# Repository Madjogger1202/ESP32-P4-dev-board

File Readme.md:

# ESP32-P4-dev-board

> High-performance vision and control board based on **ESP32-P4 (32 MB internal RAM)**.  
> Designed as a modern replacement for **OpenMV-style boards** built on STM32H7,  
> with integrated USB interfaces, Wi-Fi, camera connector, and expansion ports.

---

## Overview

ESP32-P4-dev-board combines imaging, communication, and compute capabilities in a single compact platform.  
The board supports **MIPI camera modules**, **microSD storage**, **Wi-Fi via ESP-WROOM-02**, and multiple USB interfaces for flexible development and deployment.

---

## Key Features

- **Main MCU:** ESP32-P4 (dual-core, 32 MB integrated PSRAM)
- **External Flash:** GD25Q256EYIGR (32 MByte QSPI)
- **Wi-Fi module:** ESP-WROOM-02 (UART connection to P4)
- **Distance sensor:** VL53L0CXV0DH1 (time-of-flight)
- **Camera interface:** DF30FC-24DS-0.4V_81 (2-lane MIPI, Raspberry Pi-compatible)
- **microSD slot:** 4-bit SDIO
- **5× WS2812B RGB LEDs** — for illumination or status visualization
- **Three USB ports:**
  - **USB-UART** (CH343P, auto-programming transistors)
  - **USB FS** — GPIO 24 / 25
  - **USB HS** — native high-speed
- **Expansion:**
  - Unused GPIOs routed to headers
  - Dedicated UART and I²C headers for peripheral modules
- **Design:** fully compliant with **ГОСТ** electrical documentation standards

---

## MCU Comparison — ESP32-P4 vs STM32H743 (OpenMV reference)

| Feature | **ESP32-P4** | **STM32H743 (OpenMV)** |
|:--|:--|:--|
| Architecture | Dual-core Xtensa LX7 | Single-core ARM Cortex-M7 |
| Clock frequency | up to **400 MHz** | up to **480 MHz** |
| Internal RAM | **32 MB unified PSRAM** | **1 MB SRAM** |
| External memory | QSPI Flash (32 MB) | QSPI Flash (32 MB external PSRAM optional) |
| Floating-point | Yes, single precision | Yes, single/double precision |
| SIMD / Vector | Yes (DSP extensions) | Yes |
| MIPI Camera | **2-lane CSI** | Parallel DCMI only |
| USB | **Dual USB (FS + HS)** | USB FS only |
| Wi-Fi / BT | External (ESP-WROOM-02) | None |
| Power domains | Integrated PMU | External regulators |
| Peripherals | I²S, SPI, I²C, SDIO, PWM, UART | I²S, SPI, I²C, SDIO, UART |
| Typical RAM bandwidth | ~3.2 GB/s internal | ~200 MB/s SRAM |
| Cost efficiency | Higher performance per $ | Mature ecosystem |
| OpenMV compatibility | Target-compatible (similar form-factor) | Native reference platform |

> ✅ **ESP32-P4** outperforms STM32H7 in memory bandwidth and integration,  
> enabling higher-resolution image processing and neural inference directly on-board.

---

## Power & Interfaces

| Function | Interface | Notes |
|:--|:--|:--|
| Power | USB-C / USB-UART | 5 V input |
| Programming | via CH343P (auto-boot/reset) | |
| Storage | microSD (SDIO 4-bit) | High-speed mode supported |
| Wi-Fi | ESP-WROOM-02 | UART link |
| Camera | MIPI-CSI 2-lane | Supports low-cost Pi-compatible modules |
| Distance sensor | VL53L0CXV0DH1 | I²C |
| LEDs | WS2812B × 5 | GPIO-controlled |
| Expansion | UART, I²C, GPIO headers | For custom peripherals |

---

## Typical Applications

- Embedded **computer-vision** systems  
- **Robot control** and sensor fusion nodes  
- **Edge AI** and object-tracking experiments  
- Low-cost camera systems for prototyping and teaching  
- Drop-in **OpenMV replacement** with better memory and bandwidth

---

## Quick Use

1. Connect via **USB-UART** port for programming (auto-boot handled by CH343P).  
2. Flash firmware (ESP-IDF, MicroPython, or custom).  
3. Connect MIPI camera module to DF30FC-24DS connector.  
4. Optionally mount **microSD** for data logging.  
5. Power from any USB port (5 V).  
6. Use WS2812B LEDs for illumination or debug status.

---

## Notes

- Default PD profile: **5 V** (no PD negotiation required).  
- **ESP-WROOM-02** communicates only over UART (no SPI bridge).  
- **MIPI interface** is 2-lane, matching most low-cost Raspberry Pi-compatible cameras.  
- **Schematics and layout** follow ГОСТ formatting.  
- **All unconnected GPIOs** are routed to headers for expansion.

---

## Images
*(to be added)*  
- Board top view  
- Board bottom view  
- Top layer routing  

---

## ⚠️ Status

> ⚠️ This hardware is **unverified** — first prototype **not yet tested**.  
> Electrical connections and functionality may require validation and tuning.

---

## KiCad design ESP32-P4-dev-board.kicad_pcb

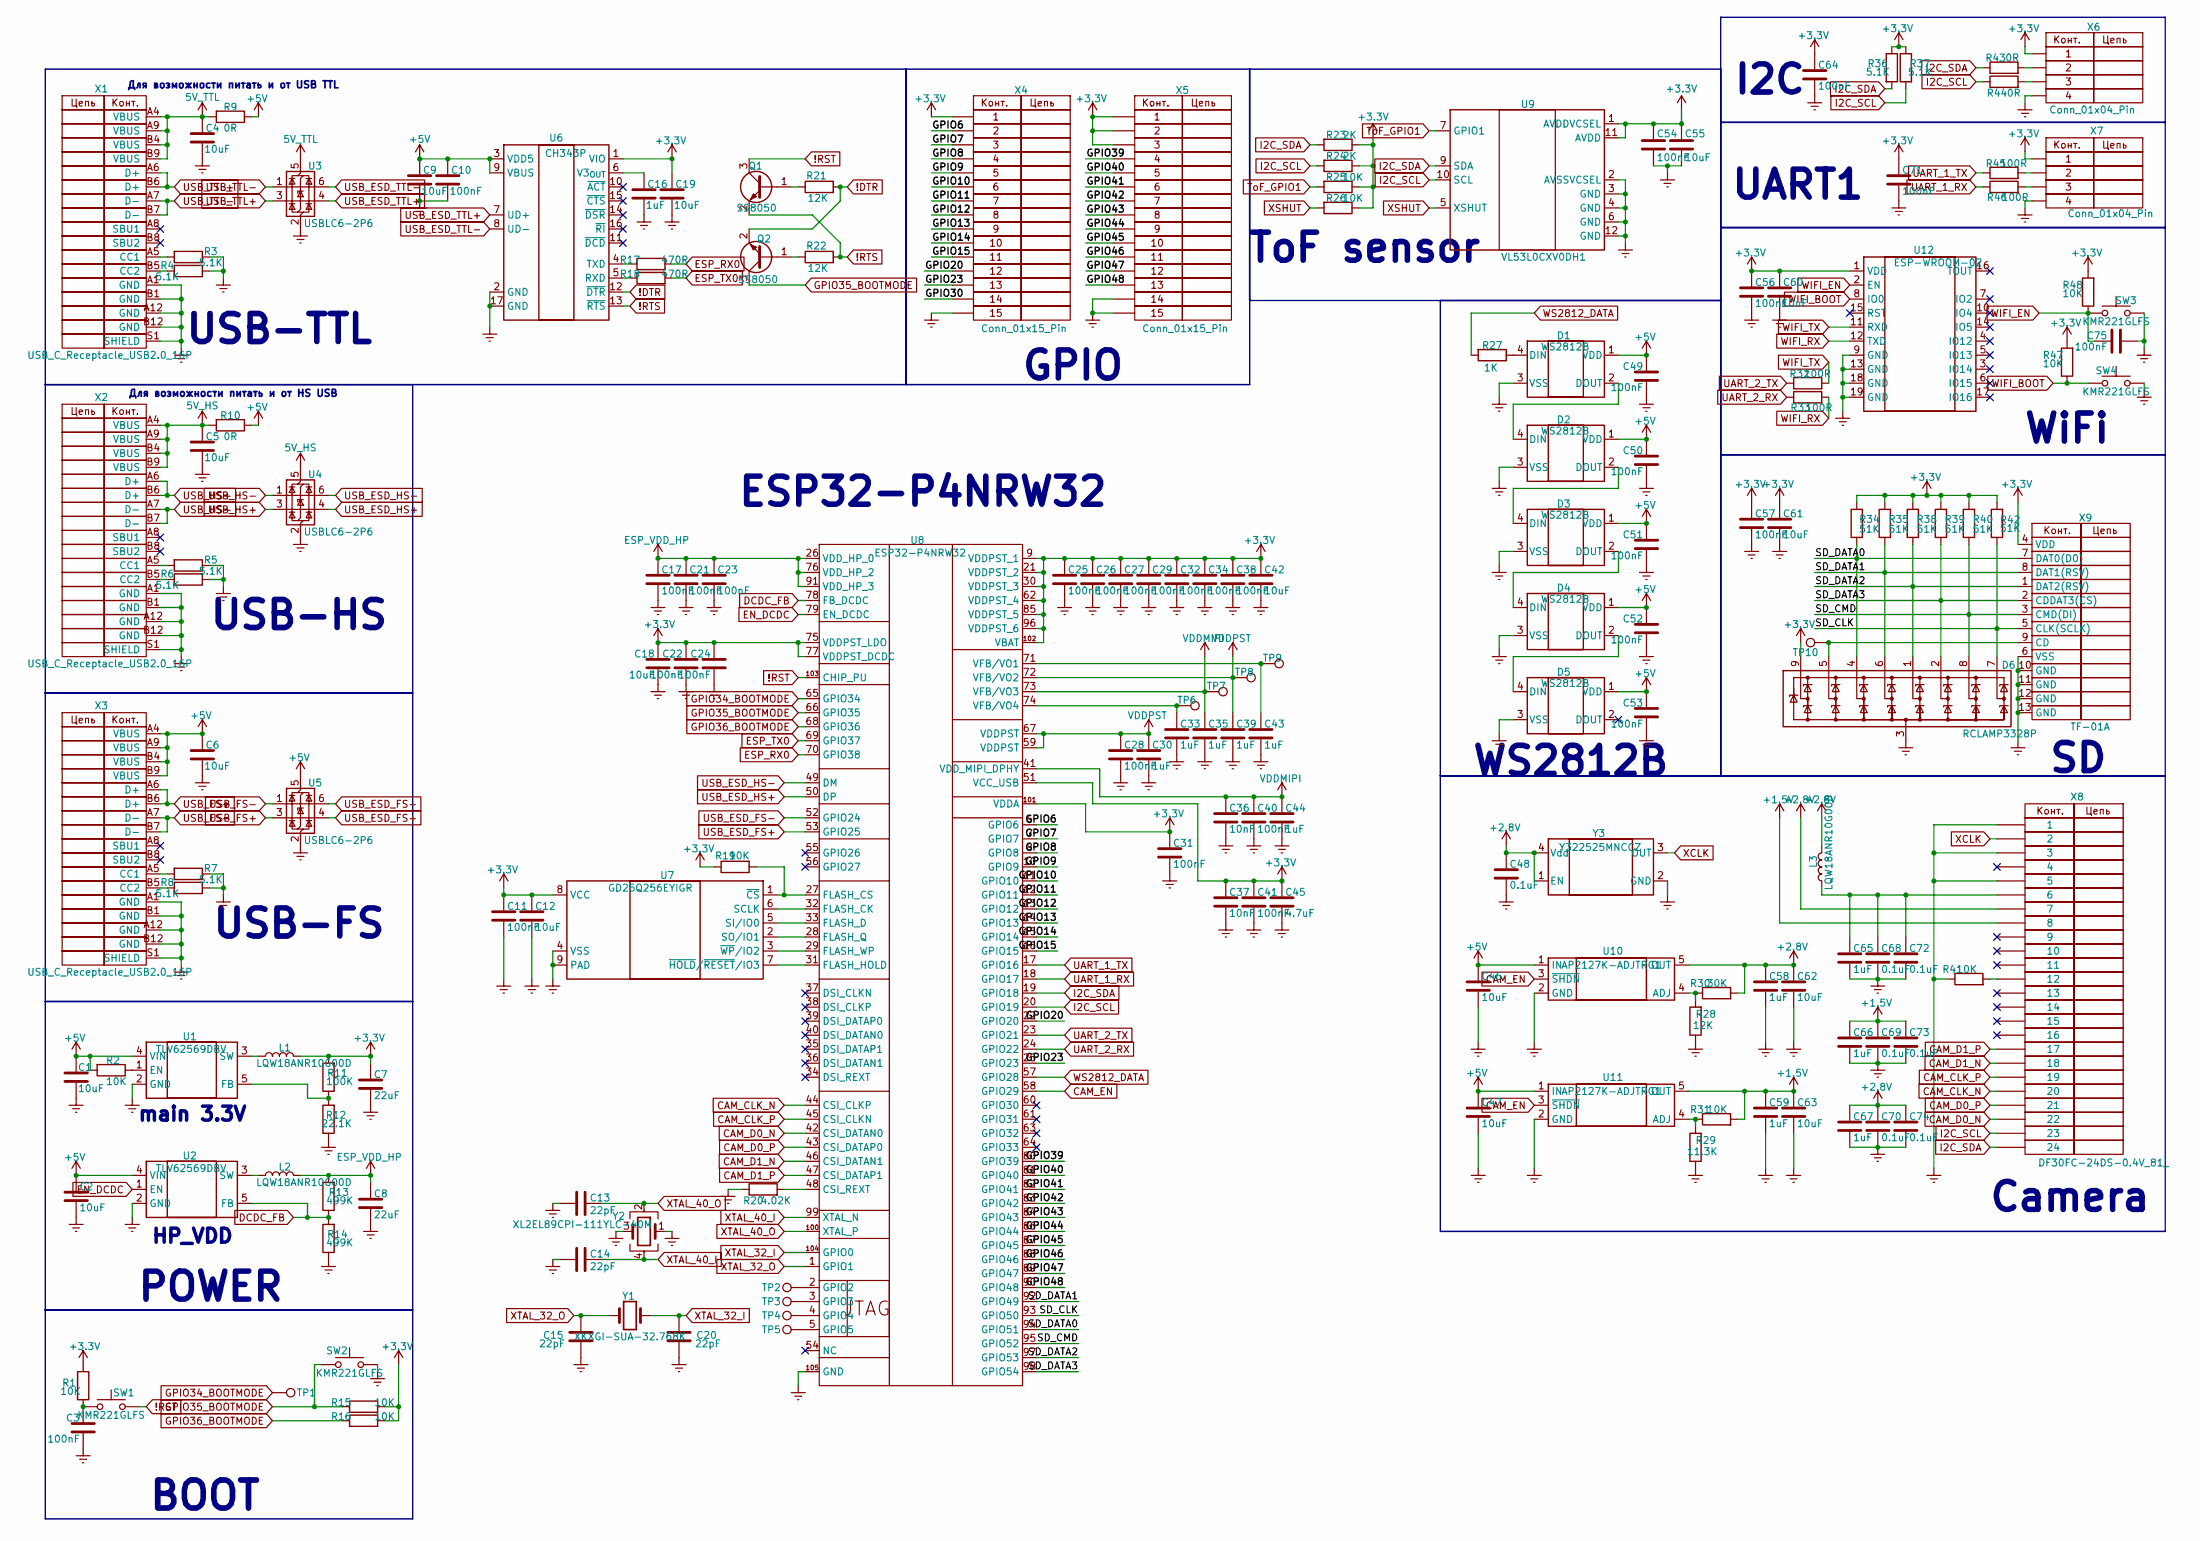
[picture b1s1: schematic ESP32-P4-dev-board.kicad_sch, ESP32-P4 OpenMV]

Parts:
C1, C2, C4, C5, C6, C9, C12, C18, C19, C42, C46, C47, C55, C60, C61, C62, C63: 10uF; C_0402_1005Metric
C3, C10, C11, C17, C21, C22, C23, C24, C25, C26, C27, C28, C29, C31, C32, C34, C38, C40, C41, C49, C50, C51, C52, C53, C54, C56, C57, C64, C71, C75: 100nF; C_0402_1005Metric
C7, C8: 22uF; C_0402_1005Metric
C13, C14, C15, C20: 22pF; C_0402_1005Metric
C16, C30, C33, C35, C39, C43, C44, C58, C59, C65, C66, C67: 1uF; C_0402_1005Metric
C36, C37: 10nF; C_0402_1005Metric
C45: 4.7uF; C_0402_1005Metric
C48, C68, C69, C70, C72, C73, C74: 0.1uF; C_0402_1005Metric
D1, D2, D3, D4, D5: WS2812B; LED_WS2812B_PLCC4_5.0x5.0mm_P3.2mm
D6: RCLAMP3328P; UDFN-9_1.0x3.8mm_P0.5mm
L1, L2: LQW18ANR10G00D; L_Wurth_WE-LQSH-3012
L3: LQW18ANR10G00D; L_0603_1608Metric
Q1, Q2: SS8050; SOT-23
R1, R2, R15, R16, R19, R25, R26, R31, R41, R47, R48: 10K; R_0402_1005Metric
R3, R4, R5, R6, R7, R8, R36, R37: 5.1K; R_0402_1005Metric
R9, R10: 0R; R_0603_1608Metric
R11: 100K; R_0402_1005Metric
R12: 22.1K; R_0402_1005Metric
R13, R14: 499K; R_0402_1005Metric
R17, R18: 470R; R_0402_1005Metric
R20: 4.02K; R_0402_1005Metric
R21, R22, R28: 12K; R_0402_1005Metric
R23, R24: 2K; R_0402_1005Metric
R27: 1K; R_0402_1005Metric
R29: 11.3K; R_0402_1005Metric
R30: 30K; R_0402_1005Metric
R32, R33, R45, R46: 100R; R_0402_1005Metric
R34, R35, R38, R39, R40, R42: 51K; R_0402_1005Metric
R43, R44: 0R; R_0402_1005Metric
SW1, SW2, SW3, SW4: KMR221GLFS; SW_SPST_PTS810
TP1, TP2, TP3, TP4, TP5, TP6, TP7, TP8, TP9, TP10: TestPoint; TestPoint_Pad_D1.0mm
U1, U2: TLV62569DBV; SOT-23-5
U3, U4, U5: USBLC6-2P6; SOT-666
U6: CH343P; WCH_QFN-16-1EP_3x3mm_P0.5mm_EP1.8x1.8mm
U7: GD25Q256EYIGR; WSON-8-1EP_8x6mm_P1.27mm_EP3.4x4.3mm
U8: ESP32-P4NRW32; Manufacturer Part ESP32-P4NRW32; LCSC Part Name ESP32-P4NRW32
U9: VL53L0CXV0DH1; ST_VL53L1x
U10, U11: AP2127K-ADJTRG1; SOT-23-5
U12: ESP-WROOM-02
X1, X2, X3: USB_C_Receptacle_USB2.0_16P; USB_C_Receptacle_GCT_USB4105-xx-A_16P_TopMnt_Horizontal
X4, X5: Conn_01x15_Pin; PinSocket_1x15_P1.27mm_Vertical
X6, X7: Conn_01x04_Pin; PinHeader_1x04_P2.54mm_Vertical
X8: DF30FC-24DS-0.4V_81_; DF30FC-24DS-0.4V(81); Manufacturer_Part_Number DF30FC-24DS-0.4V(81); Mouser Part Number 798-DF30FC24DS04V81
X9: TF-01A; Manufacturer Part TF-01A; LCSC Part Name 自弹式 MicroSD卡(TF卡) 卡座
Y1: XKXGI-SUA-32.768K; Crystal_SMD_3215-2Pin_3.2x1.5mm
Y2: XL2EL89CPI-111YLC-40M; Crystal_SMD_3225-4Pin_3.2x2.5mm
Y3: Y322525MNCCZ; Oscillator_SMD_Abracon_ASE-4Pin_3.2x2.5mm

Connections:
5V_HS: C5.1, R10.2, U4.5 (VBUS), X2.A4 (VBUS), X2.A9 (VBUS), X2.B4 (VBUS), X2.B9 (VBUS)
5V_TTL: C4.1, R9.2, U3.5 (VBUS), X1.A4 (VBUS), X1.A9 (VBUS), X1.B4 (VBUS), X1.B9 (VBUS)
!DTR: Q2.2 (E), R21.2, U6.12 (~DTR)
!RST: Q1.3 (C), SW1.2, U8.103 (CHIP_PU)
!RTS: Q1.2 (E), R22.2, U6.13 (~RTS)
+1.5V: C59.1, C63.1, C66.1, C69.1, C73.1, R31.2, U11.5 (OUT), X8.8
+2.8V: C48.1, C58.1, C62.1, C67.1, C70.1, C74.1, L3.1, R30.2, U10.5 (OUT), X8.7, Y3.1 (EN), Y3.4 (Vdd)
+3.3V: C7.1, C11.1, C12.1, C18.1, C19.1, C22.1, C24.1, C25.1, C26.1, C27.1, C29.1, C31.1, C32.1, C34.1, C37.1, C38.1, C41.1, C42.1, C45.1, C54.1, C55.1, C56.1, C57.1, C60.1, C61.1, C64.1, C71.1, D6.9 (K8), L1.1, R1.2, R11.2, R15.2, R16.2, R19.1, R23.1, R24.1, R25.1, R26.1, R34.2, R35.2, R36.1, R37.1, R38.2, R39.2, R40.2, R42.2, R47.2, R48.2, U6.1 (VIO), U7.8 (VCC), U8.9 (VDDPST_1), U8.21 (VDDPST_2), U8.30 (VDDPST_3), U8.51 (VCC_USB), U8.62 (VDDPST_4), U8.75 (VDDPST_LDO), U8.77 (VDDPST_DCDC), U8.85 (VDDPST_5), U8.96 (VDDPST_6), U8.101 (VDDA), U8.102 (VBAT), U9.1 (AVDDVCSEL), U9.11 (AVDD), U12.1 (VDD), X4.1, X5.1, X5.2, X5.3, X6.1, X7.1, X9.4 (VDD)
+5V: C1.1, C2.1, C6.1, C9.1, C10.1, C46.1, C47.1, C49.1, C50.1, C51.1, C52.1, C53.1, D1.1 (VDD), D2.1 (VDD), D3.1 (VDD), D4.1 (VDD), D5.1 (VDD), R2.2, R9.1, R10.1, U1.4 (VIN), U2.4 (VIN), U5.5 (VBUS), U6.3 (VDD5), U6.9 (VBUS), U10.1 (IN), U11.1 (IN), X3.A4 (VBUS), X3.A9 (VBUS), X3.B4 (VBUS), X3.B9 (VBUS)
/GPIO6: U8.6 (GPIO6), X4.2
/GPIO7: U8.7 (GPIO7), X4.3
/GPIO8: U8.8 (GPIO8), X4.4
/GPIO9: U8.10 (GPIO9), X4.5
/GPIO10: U8.11 (GPIO10), X4.6
/GPIO11: U8.12 (GPIO11), X4.7
/GPIO12: U8.13 (GPIO12), X4.8
/GPIO13: U8.14 (GPIO13), X4.9
/GPIO14: U8.15 (GPIO14), X4.10
/GPIO15: U8.16 (GPIO15), X4.11
/GPIO20: U8.22 (GPIO20), X4.12
/GPIO23: U8.25 (GPIO23), X4.13
/GPIO30: X4.14
/GPIO39: U8.80 (GPIO39), X5.4
/GPIO40: U8.81 (GPIO40), X5.5
/GPIO41: U8.82 (GPIO41), X5.6
/GPIO42: U8.83 (GPIO42), X5.7
/GPIO43: U8.84 (GPIO43), X5.8
/GPIO44: U8.86 (GPIO44), X5.9
/GPIO45: U8.87 (GPIO45), X5.10
/GPIO46: U8.88 (GPIO46), X5.11
/GPIO47: U8.89 (GPIO47), X5.12
/GPIO48: U8.90 (GPIO48), X5.13
/SD_CLK: D6.7 (K6), R42.1, U8.93 (GPIO50), X9.5 (CLK(SCLK))
/SD_CMD: D6.8 (K7), R40.1, U8.95 (GPIO52), X9.3 (CMD(DI))
/SD_DATA0: D6.4 (K3), R34.1, U8.94 (GPIO51), X9.7 (DAT0(D0))
/SD_DATA1: D6.6 (K5), R35.1, U8.92 (GPIO49), X9.8 (DAT1(RSV))
/SD_DATA2: D6.1 (K1), R38.1, U8.97 (GPIO53), X9.1 (DAT2(RSV))
/SD_DATA3: D6.2 (K2), R39.1, U8.98 (GPIO54), X9.2 (CDDAT3(CS))
CAM_CLK_N: U8.44 (CSI_CLKP), X8.20
CAM_CLK_P: U8.45 (CSI_CLKN), X8.19
CAM_D0_N: U8.42 (CSI_DATAN0), X8.22
CAM_D0_P: U8.43 (CSI_DATAP0), X8.21
CAM_D1_N: U8.46 (CSI_DATAN1), X8.18
CAM_D1_P: U8.47 (CSI_DATAP1), X8.17
CAM_EN: U8.58 (GPIO29), U10.3 (~SHDN), U11.3 (~SHDN)
DCDC_FB: R13.1, R14.2, U2.5 (FB), U8.78 (FB_DCDC)
EN_DCDC: U2.1 (EN), U8.79 (EN_DCDC)
ESP_RX0: R17.2, U8.70 (GPIO38)
ESP_TX0: R18.2, U8.69 (GPIO37)
ESP_VDD_HP: C8.1, C17.1, C21.1, C23.1, L2.1, R13.2, U8.26 (VDD_HP_0), U8.76 (VDD_HP_2), U8.91 (VDD_HP_3)
Earth: C1.2, C2.2, C3.2, C4.2, C5.2, C6.2, C7.2, C8.2, C9.2, C10.2, C11.2, C12.2, C13.2, C14.2, C15.1, C16.2, C17.2, C18.2, C19.2, C20.1, C21.2, C22.2, C23.2, C24.2, C25.2, C26.2, C27.2, C28.2, C29.2, C30.2, C31.2, C32.2, C33.2, C34.2, C35.2, C36.2, C37.2, C38.2, C39.2, C40.2, C41.2, C42.2, C43.2, C44.2, C45.2, C46.2, C47.2, C48.2, C49.2, C50.2, C51.2, C52.2, C53.2, C54.2, C55.2, C56.2, C57.2, C58.2, C59.2, C60.2, C61.2, C62.2, C63.2, C64.2, C65.2, C66.2, C67.2, C68.2, C69.2, C70.2, C71.2, C72.2, C73.2, C74.2, C75.2, D1.3 (VSS), D2.3 (VSS), D3.3 (VSS), D4.3 (VSS), D5.3 (VSS), D6.3 (A), R3.1, R4.2, R5.1, R6.2, R7.1, R8.2, R12.1, R14.1, R20.1, R28.1, R29.1, R41.1, SW2.1, SW3.1, SW4.2, U1.2 (GND), U2.2 (GND), U3.2 (GND), U4.2 (GND), U5.2 (GND), U6.2 (GND), U6.17 (GND), U7.4 (VSS), U7.9 (PAD), U8.105 (GND), U9.2 (AVSSVCSEL), U9.3 (GND), U9.4 (GND), U9.6 (GND), U9.12 (GND), U10.2 (GND), U11.2 (GND), U12.9 (GND), U12.13 (GND), U12.18 (GND), U12.19 (GND), X1.A1 (GND), X1.A12 (GND), X1.B1 (GND), X1.B12 (GND), X1.S1 (SHIELD), X2.A1 (GND), X2.A12 (GND), X2.B1 (GND), X2.B12 (GND), X2.S1 (SHIELD), X3.A1 (GND), X3.A12 (GND), X3.B1 (GND), X3.B12 (GND), X3.S1 (SHIELD), X4.15, X5.14, X5.15, X6.4, X7.4, X8.1, X8.3, X8.5, X9.6 (VSS), X9.10 (GND), X9.11 (GND), X9.12 (GND), X9.13 (GND), Y2.1, Y2.3, Y3.2 (GND)
GPIO34_BOOTMODE: TP1.1, U8.65 (GPIO34)
GPIO35_BOOTMODE: Q2.3 (C), R15.1, SW2.2, U8.66 (GPIO35)
GPIO36_BOOTMODE: R16.1, U8.68 (GPIO36)
I2C_SCL: R24.2, R37.2, R44.1, U8.20 (GPIO19), U9.10 (SCL), X8.23
I2C_SDA: R23.2, R36.2, R43.1, U8.19 (GPIO18), U9.9 (SDA), X8.24
unnamed: C3.1, R1.1, SW1.1
unnamed: C65.1, C68.1, C72.1, L3.2, X8.6
unnamed: D1.4 (DIN), R27.1
unnamed: D1.2 (DOUT), D2.4 (DIN)
unnamed: D2.2 (DOUT), D3.4 (DIN)
unnamed: D3.2 (DOUT), D4.4 (DIN)
unnamed: D4.2 (DOUT), D5.4 (DIN)
unnamed: D6.5 (K4), TP10.1, X9.9 (CD)
unnamed: Q1.1 (B), R21.1
unnamed: Q2.1 (B), R22.1
unnamed: R41.2, X8.12
unnamed: R2.1, U1.1 (EN)
unnamed: R11.1, R12.2, U1.5 (FB)
unnamed: L1.2, U1.3 (SW)
unnamed: L2.2, U2.3 (SW)
unnamed: R18.1, U6.5 (RXD)
unnamed: R17.1, U6.4 (TXD)
unnamed: C16.1, U6.6 (V3_{OUT})
unnamed: U7.6 (SCLK), U8.32 (FLASH_CK)
unnamed: U7.5 (SI/IO0), U8.33 (FLASH_D)
unnamed: U7.2 (SO/IO1), U8.28 (FLASH_Q)
unnamed: R19.2, U7.1 (~CS), U8.27 (FLASH_CS)
unnamed: U7.7 (~HOLD/~RESET/IO3), U8.31 (FLASH_HOLD)
unnamed: U7.3 (~WP/IO2), U8.29 (FLASH_WP)
unnamed: R20.2, U8.48 (CSI_REXT)
unnamed: TP2.1, U8.2 (GPIO2)
unnamed: TP3.1, U8.3 (GPIO3)
unnamed: TP4.1, U8.4 (GPIO4)
unnamed: TP5.1, U8.5 (GPIO5)
unnamed: C43.1, TP9.1, U8.71 (VFB/VO1)
unnamed: C33.1, TP6.1, U8.74 (VFB/VO4)
unnamed: R28.2, R30.1, U10.4 (ADJ)
unnamed: R29.2, R31.1, U11.4 (ADJ)
unnamed: R3.2, X1.A5 (CC1)
unnamed: R4.1, X1.B5 (CC2)
unnamed: R5.2, X2.A5 (CC1)
unnamed: R6.1, X2.B5 (CC2)
unnamed: R7.2, X3.A5 (CC1)
unnamed: R8.1, X3.B5 (CC2)
unnamed: R43.2, X6.2
unnamed: R44.2, X6.3
unnamed: R45.2, X7.2
unnamed: R46.2, X7.3
ToF_GPIO1: R25.2, U9.7 (GPIO1)
UART_1_RX: R46.1, U8.18 (GPIO17)
UART_1_TX: R45.1, U8.17 (GPIO16)
UART_2_RX: R33.1, U8.24 (GPIO22)
UART_2_TX: R32.1, U8.23 (GPIO21)
USB_ESD_FS+: U5.4 (I/O2), U8.53 (GPIO25)
USB_ESD_FS-: U5.6 (I/O1), U8.52 (GPIO24)
USB_ESD_HS+: U4.4 (I/O2), U8.50 (DP)
USB_ESD_HS-: U4.6 (I/O1), U8.49 (DM)
USB_ESD_TTL+: U3.4 (I/O2), U6.7 (UD+)
USB_ESD_TTL-: U3.6 (I/O1), U6.8 (UD-)
USB_FS+: U5.3 (I/O2), X3.A6 (D+), X3.B6 (D+)
USB_FS-: U5.1 (I/O1), X3.A7 (D-), X3.B7 (D-)
USB_HS+: U4.3 (I/O2), X2.A6 (D+), X2.B6 (D+)
USB_HS-: U4.1 (I/O1), X2.A7 (D-), X2.B7 (D-)
USB_TTL+: U3.3 (I/O2), X1.A6 (D+), X1.B6 (D+)
USB_TTL-: U3.1 (I/O1), X1.A7 (D-), X1.B7 (D-)
VDDMIPI: C35.1, C36.1, C40.1, C44.1, TP7.1, U8.41 (VDD_MIPI_DPHY), U8.73 (VFB/VO3)
VDDPST: C28.1, C30.1, C39.1, TP8.1, U8.59 (VDDPST), U8.67 (VDDPST), U8.72 (VFB/VO2)
WIFI_BOOT: R47.1, SW4.1, U12.8 (IO0)
WIFI_EN: C75.1, R48.1, SW3.2, U12.2 (EN)
WIFI_RX: R33.2, U12.12 (TXD)
WIFI_TX: R32.2, U12.11 (RXD)
WS2812_DATA: R27.2, U8.57 (GPIO28)
XCLK: X8.2, Y3.3 (OUT)
XSHUT: R26.2, U9.5 (XSHUT)
XTAL_32_I: C20.2, U8.104 (GPIO0), Y1.2
XTAL_32_O: C15.2, U8.1 (GPIO1), Y1.1
XTAL_40_I: C14.1, U8.99 (XTAL_N), Y2.4
XTAL_40_O: C13.1, U8.100 (XTAL_P), Y2.2

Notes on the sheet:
Для возможности питать и от USB TTL
POWER
UART1
main 3.3V
HP_VDD
BOOT
Camera
WS2812B
USB-TTL
ToF sensor
I2C
Для возможности питать и от HS USB
WiFi
USB-HS
GPIO
ESP32-P4NRW32
USB-FS

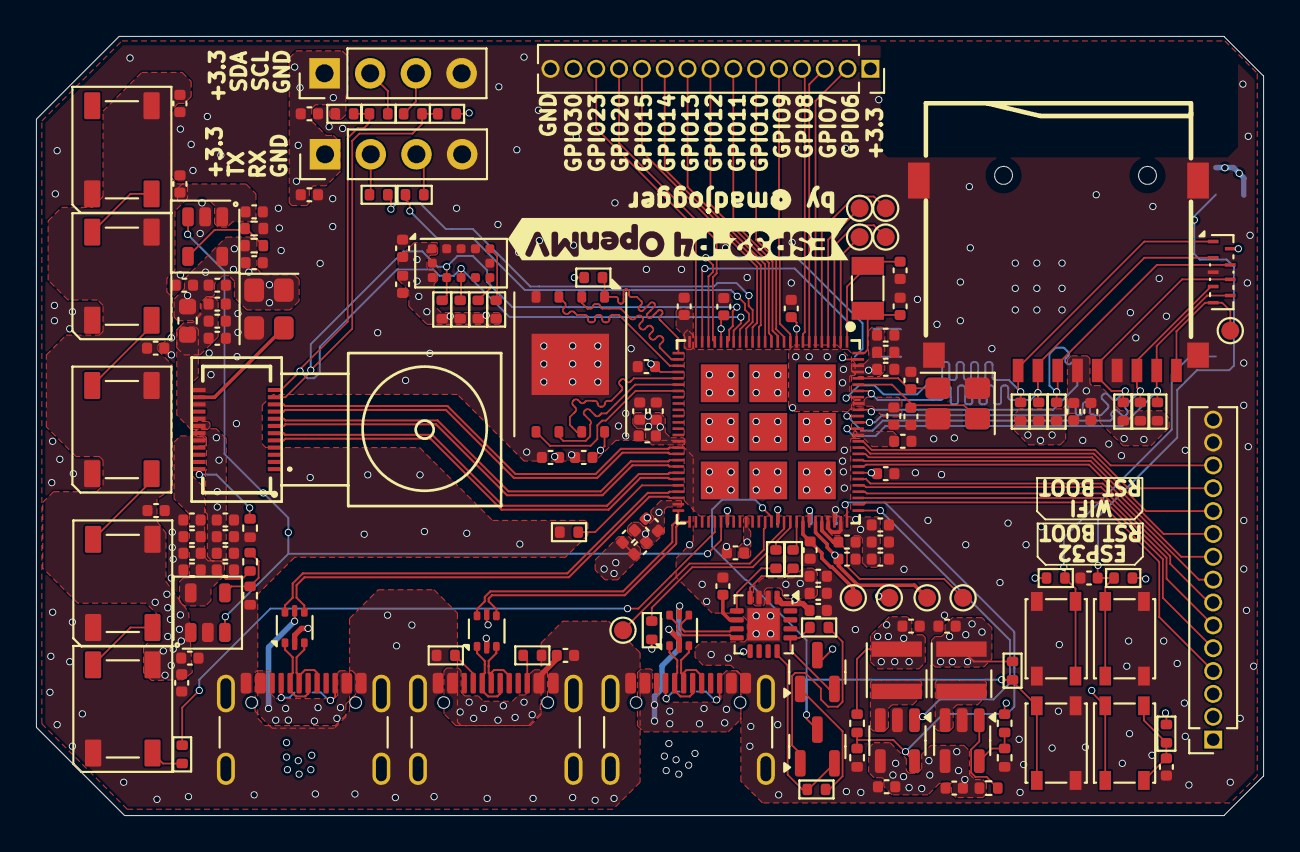
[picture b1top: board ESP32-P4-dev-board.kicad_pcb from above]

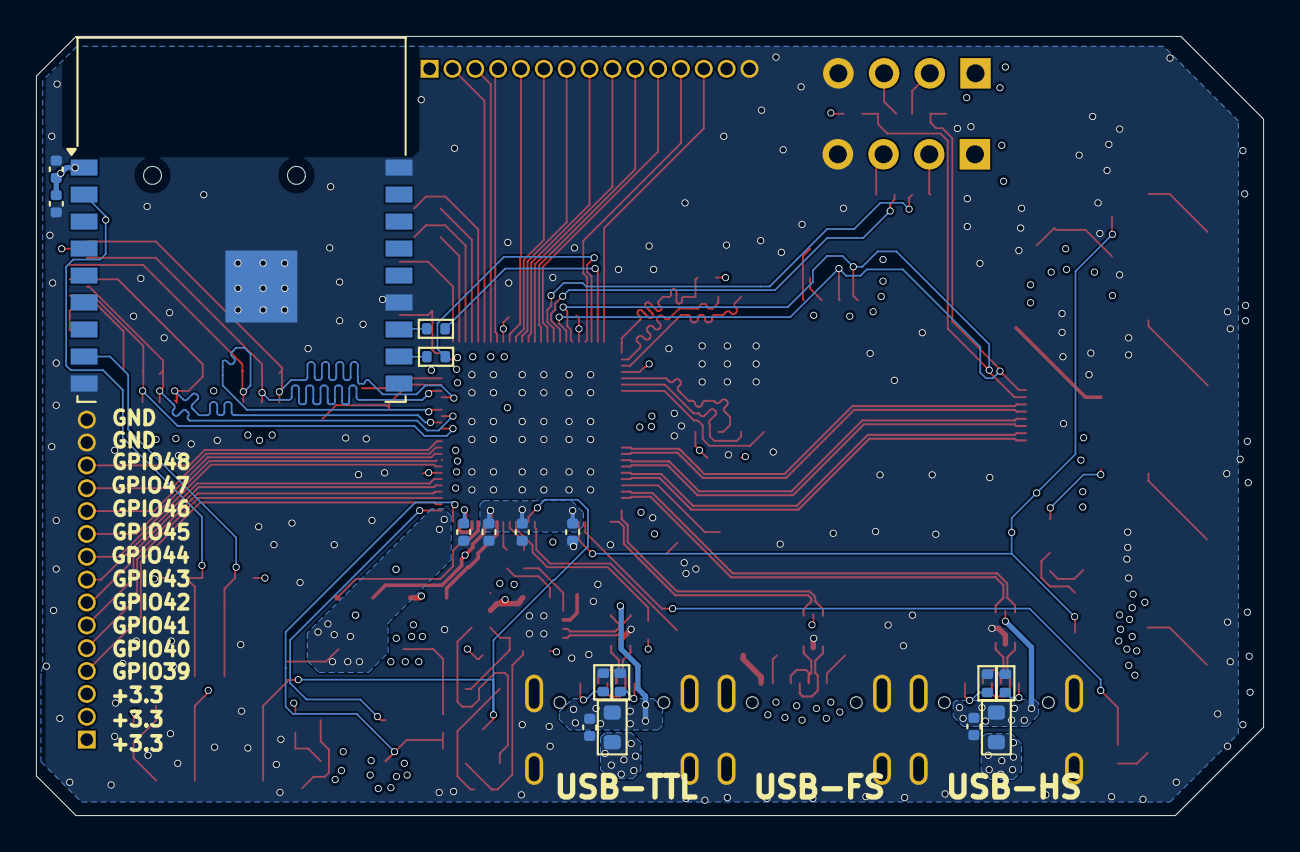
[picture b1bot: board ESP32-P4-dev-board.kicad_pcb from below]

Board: 4 copper layers, 68.2 x 43.3 mm, 173 parts (17 on the bottom side), 128 nets.

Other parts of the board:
kibuzzard-6926A799: G***; kibuzzard-6926A799

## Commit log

2025-11-24 schematics ready
2025-11-25 трассировка и проверка завершены
2025-11-26 Rev 0 ready
2025-11-26 added README
